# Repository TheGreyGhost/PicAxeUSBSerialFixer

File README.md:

# PicAxeUSBSerialFixer
 Circuit to program the PICaxe using a standard USB to Serial converter.
 
 The PICAxe requires a particular download USB-to-serial cable (https://picaxe.com/hardware/cables/picaxe-usb-download-cable)
 
 If (like me) you already have another USB-to-serial adapter, you will probably find that it does not work properly - 
 program downloads won't start.
 
 The reason is that the PICAXE requires a Serial Break signal in order to start communicating with the programmer.
 A Serial Break is where the PICAXE serial input is set to high for longer than a single frame (~ 12 bits)
 A normal serial byte has a start bit (high), 8 bits of data (high or low), then several stop bits.
 
 When the PICAXE detects that the serial input has been high for longer than a frame, it enters a program ready mode:
 While the input is held high, every second or it sends a signature block on the serial output (chip type and 
 other information) and waits for further transmission.
 
 Some USB-to-serial adapters don't send a serial break, so the PICAXE never enters programming mode.
 
 With some deft timing and patience this can be done manually - start a download, briefly short the serial input to 5V with a 10k resistor and with a 
 bit of luck the download will work.  Unless your PICAXE needs all five pins and hence uses the disconnect command, in which case it is a real pain in butt.
 
Alternatively you can use a PICAXE "SerialFixer" to add a serial break:
Step by step:
 1) Connect PC to PICAXEprogrammer and PICAXEprogrammer to the PICAXE to be programmed
 2) Power up the PICAXEprogrammer
 2a) Optional: Power up the PICAXE to be programmed, if it doesn't use the disconnect command
 3) Start the program download.  The PICAXEprogrammer will start sending a break.
 3a) Optional: if the PICAXE to be programmed isn't already on, turn it on now
 4) Once the PICAXEprogrammer detects a reply from the PICAXE being programmed, it stops sending break and will pass through
    the transmission from the PC to the PICAXE.
 5) Once the programming is finished, the PICAXEprogrammer will start idling again.

It's not 100% reliable- you may need to try the download a couple of times, but in my experience most of the time it will work first attempt.      

The jumper on the SerialFixer board can be used to disable the break, i.e.:
Jumper not installed = insert serial break
Jumper installed = passthrough only (do not insert a break)

## Footnote
You might be asking yourself why I went to all this trouble?

I'd have to have rocks in my head given that the official AXE027 cable (https://picaxe.com/hardware/cables/picaxe-usb-download-cable/) costs a lot less
than the time and effort to build this circuit!

Unless, of course, COVID-19 had pushed out the estimated delivery time to 3 months...

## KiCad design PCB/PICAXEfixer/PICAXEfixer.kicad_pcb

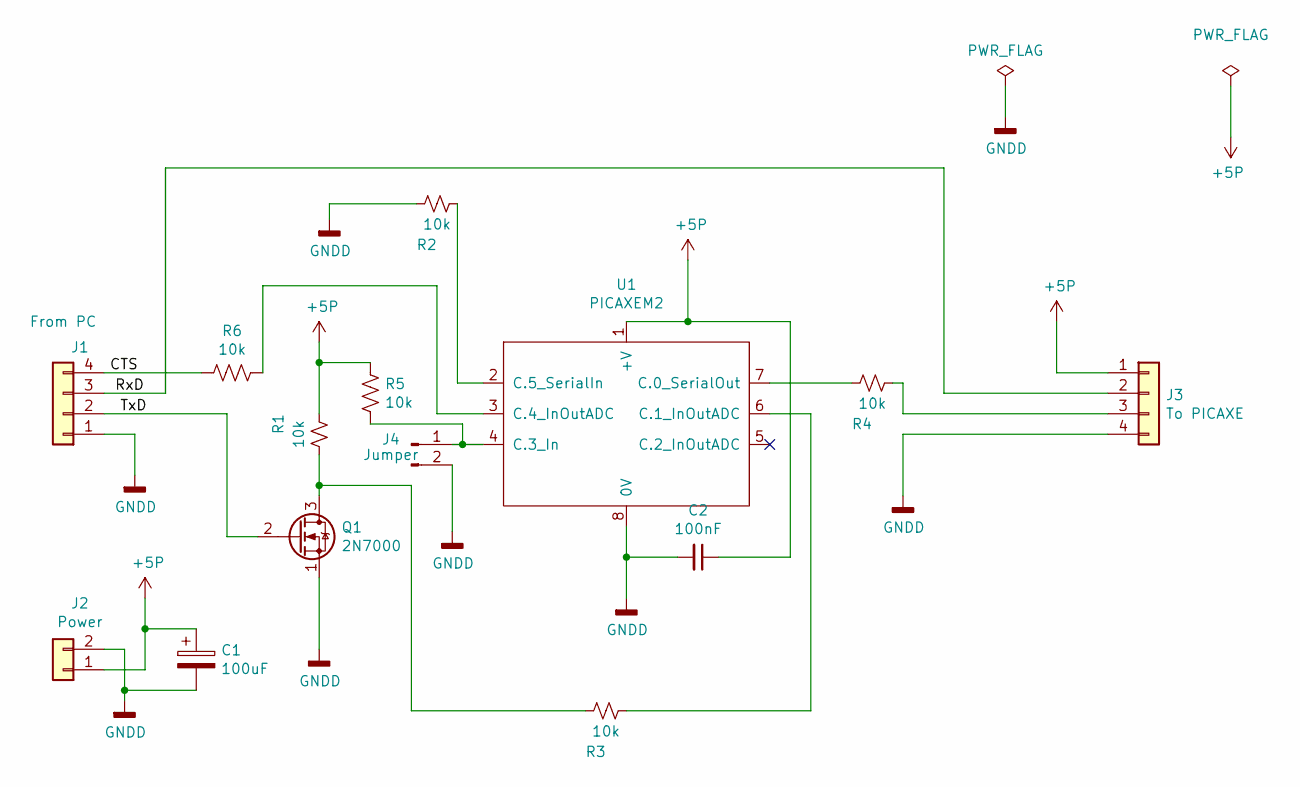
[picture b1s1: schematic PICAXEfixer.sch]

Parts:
C1: 100uF; CP_Radial_D10.0mm_P7.50mm
C2: 100nF; C_Disc_D7.5mm_W5.0mm_P10.00mm
J1: From PC; PinHeader_1x04_P2.54mm_Vertical
J2: Power; BarrelJack_Wuerth_6941xx301002
J3: To PICAXE; PinHeader_1x04_P2.54mm_Vertical
J4: Jumper; PinHeader_1x02_P2.54mm_Vertical
Q1: 2N7000; TO-92_Inline
R1, R2, R3, R4, R5, R6: 10k; R_Axial_DIN0309_L9.0mm_D3.2mm_P15.24mm_Horizontal
U1: PICAXEM2; DIP-8_W7.62mm

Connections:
+5P: C1.1, C2.1, J2.1, J3.1, R1.2, R5.1, U1.1 (+V)
/CTS: J1.4, R6.2
/RxD: J1.3, J3.2
/TxD: J1.2, Q1.2 (G)
GNDD: C1.2, C2.2, J1.1, J2.2, J3.4, J4.2, Q1.1 (S), R2.2, U1.8 (0V)
unnamed: J3.3, R4.1
unnamed: J4.1, R5.2, U1.4 (C.3_In)
unnamed: Q1.3 (D), R1.1, R3.2
unnamed: R2.1, U1.2 (C.5_SerialIn)
unnamed: R3.1, U1.6 (C.1_InOutADC)
unnamed: R4.2, U1.7 (C.0_SerialOut)
unnamed: R6.1, U1.3 (C.4_InOutADC)

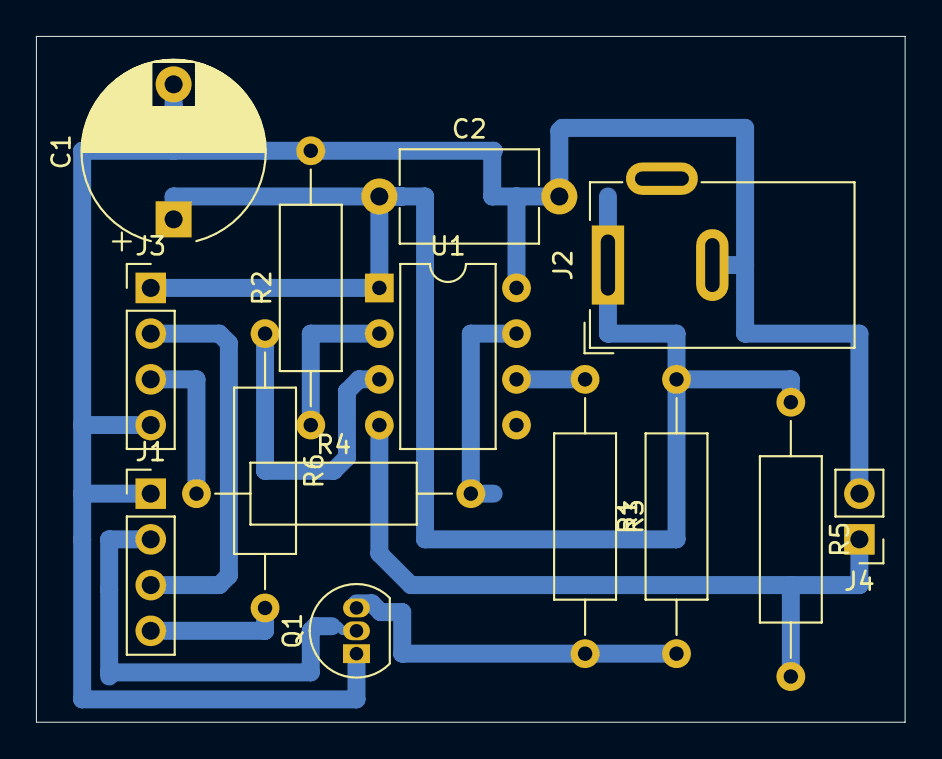
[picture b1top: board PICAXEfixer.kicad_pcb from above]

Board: 2 copper layers, 48.3 x 38.1 mm, 14 parts (0 on the bottom side), 12 nets.

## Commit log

2021-10-22 initial setup
2021-10-25 Code and circuit tested; works.
2021-10-25 pcb laying out
2021-10-26 PCB laid out
2021-10-28 final
2021-12-06 Circuit built & testing, functions erratically :/
2021-12-09 troubleshooting
2022-01-04 Mostly works. Not 100% reliable but succeeds within a couple of attempts
2022-01-06 about to try CTS
2022-01-06 Ready to try CTS variant
2022-01-11 Finally works
